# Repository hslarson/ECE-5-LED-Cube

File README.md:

<hr />

## Functionality:
- The cube lights up based on the frequency spectrum of incoming audio
- Each column represents a different frequency
- The stronger the frequency component is, the more LEDs will be on in that column
- Two 3.5mm jacks allow for audio passthrough
- A knob allows for volume control at the output
- The cube will display the volume state whenever the knob is adjusted

<hr />

## Software Details
### Main Program:

- <b> loop </b>
  - Calls the nextLayer() member  function of the Multiplexer class on a preset interval
  - While we wait for the next layer to be drawn, the loop calls the subtasks() function to perform several smaller tasks required to draw the matrix
- <b>subtasks</b>
  - Each subtask referenced in this function is called once for every complete matrix that is sent to the cube. The function must be reset after every iteration
  - The first step (case 0) is calling the checkVolume() member function of the MSGEQ7 class, this decides whether the subtasks function draws a volume matrix or a spectrum matrix
  - Next, we collect the data required to construct the matrix. This is only required if we are drawing a spectrum matrix
  - Then, we construct the matrix itself. This is handled entirely by the respective classes
  - Lastly, we queue the matrix we just drew, meaning that it will be shown in the next iteration of the loop

### Multiplexer Class:

- <b>setMatrix</b>
  - Uses memcpy to either queue a new matrix or allow the queued matrix to be shown
- <b>nextLayer</b>
  - Handles the drawing of individual layers and the queuing of matrices
  - First, calls the constructData() function to format the data in a way that the registers will understand
  - Then, calls the sendData() function to send the data to the cube
- <b>constructData</b>
  - A helper function for nextLayer() that handles the mapping of output pins and the conversion of the resultant binary array to an integer array
- <b>sendToCube</b>
  - Uses the SPI bus to send the data from the constructData() function to the shift registers

### MSGEQ7 Class:

- <b>getSpectrum</b>
  - Reads data from the MSGEQ7 breakout board using analogRead()
- <b>normSpectrum</b>
  - Takes the array from the getSpectrum() function and converts from 7 channels to 36
- <b>makeSpectrumMatrix</b>
  - Maps each frequency band to a specific column of the cube
  - Applies a threshold to the raw reading to decide how many LED’s to light in each column and constructs a Boolean matrix based on this data
- <b>queueMatrix</b>
  - Calls the setMatrix() member of the Multiplexer class to queue the matrix that was built by the makeSpectrumMatrix() function

### VolumeControl Class:

- <b>checkVolume</b>
  - Uses a timer and the getVolume() function to decide whether or not to draw a volume matrix
- <b>getVolume</b>
  - Reads data from the volume potentiometer and normalizes the reading
  - Creates a running average of the normalized readings
- <b>makeVolumeMatrix</b>
  - Takes the current volume reading and creates a Boolean matrix that displays the volume as front-to-back bars that ascend each column then move from left to right to the next column
- <b>queueMatrix</b>
  - Takes the matrix that was constructed by the makeVolumeMatrix and queues it to be shown on the cube

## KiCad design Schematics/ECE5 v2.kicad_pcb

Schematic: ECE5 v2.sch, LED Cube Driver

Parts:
A1: Arduino_Nano_v3.x; Arduino_Nano
C1, C3, C4: 0.1u; C_Disc_D5.0mm_W2.5mm_P2.50mm
C2: 33p; C_Disc_D3.4mm_W2.1mm_P2.50mm
J1, J2: AudioJack3_SwitchTR; 3.5mm_stereo_audio_jack
J3, J4, J6: Conn_02x08_Odd_Even; connector_2x8_male_right_angle
J5: Barrel_Jack_MountingPin; BarrelJack_Horizontal
J7: Conn_01x02_Female; JST_PH_B2B-PH-K_1x02_P2.00mm_Vertical
Q1, Q2, Q3, Q4, Q5, Q6: 2N3904; TO-92_Inline
R1, R2, R3, R4, R5, R6, R7, R8, R9, R10, R11, R12, R15, R16, R17, R18, R21, R22, R23, R24, R25, R26, R27, R28, R29, R30, R31, R32, R33, R34, R35, R36, R37, R38, R39, R40: 470; R_Axial_DIN0207_L6.3mm_D2.5mm_P10.16mm_Horizontal
R13, R14: 22K; R_Axial_DIN0207_L6.3mm_D2.5mm_P10.16mm_Horizontal
R19, R20: 100K; R_Axial_DIN0207_L6.3mm_D2.5mm_P10.16mm_Horizontal
R41, R42, R43, R44, R45, R46: 330; R_Axial_DIN0207_L6.3mm_D2.5mm_P10.16mm_Horizontal
RV1: R_POT_QUAD; potentiometer_quad
SW1: SW_SPDT; toggle_switch_vertical
T1, T2: Transformer_1P_1S; transformer_amazon
U1, U2, U3, U5, U6: 74HC595; DIP-16_W7.62mm_Socket
U4: MSGEQ7; DIP-8_W7.62mm_Socket

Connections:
+5V: C3.1, J7.1, R19.1, RV1.9, SW1.1, U1.10 (~SRCLR), U1.16 (VCC), U2.10 (~SRCLR), U2.16 (VCC), U3.10 (~SRCLR), U3.16 (VCC), U4.1 (VDD), U5.10 (~SRCLR), U5.16 (VCC), U6.10 (~SRCLR), U6.16 (VCC)
EQ_IN: C1.1, U4.5 (IN)
EQ_OUT: A1.20 (A1), U4.3 (OUT)
EQ_RST: A1.11 (D8), U4.7 (RESET)
EQ_STROBE: A1.12 (D9), U4.4 (STROBE)
GND: A1.4 (GND), A1.29 (GND), C2.2, C3.2, C4.2, J5.2, J7.2, Q1.1 (E), Q2.1 (E), Q3.1 (E), Q4.1 (E), Q5.1 (E), Q6.1 (E), RV1.7, T1.3, T2.3, U1.8 (GND), U1.13 (~OE), U2.8 (GND), U2.13 (~OE), U3.8 (GND), U3.13 (~OE), U4.2 (VSS), U5.8 (GND), U5.13 (~OE), U6.8 (GND), U6.13 (~OE)
LYR_1: A1.5 (D2), R41.2
LYR_2: A1.6 (D3), R42.2
LYR_3: A1.7 (D4), R43.2
LYR_4: A1.8 (D5), R44.2
LYR_5: A1.9 (D6), R45.2
LYR_6: A1.10 (D7), R46.2
unnamed: C1.2, R13.1, R14.1
unnamed: C2.1, R20.1, U4.8 (CKIN)
unnamed: C4.1, U4.6 (GND)
unnamed: J1.R, RV1.3, T1.1
unnamed: J1.S, J2.S, RV1.1, RV1.4, T1.2, T2.2
unnamed: J1.T, RV1.6, T2.1
unnamed: J2.R, RV1.2
unnamed: J2.T, RV1.5
unnamed: J3.1, R2.1
unnamed: J3.2, R1.2
unnamed: J3.3, R4.1
unnamed: J3.4, R3.2
unnamed: J3.5, R6.1
unnamed: J3.6, R5.2
unnamed: J3.7, R8.1
unnamed: J3.8, R7.2
unnamed: J3.9, R10.1
unnamed: J3.10, R9.2
unnamed: J3.11, R12.1
unnamed: J3.12, R11.2
unnamed: J3.13, R16.1
unnamed: J3.14, R15.2
unnamed: J3.15, R18.1
unnamed: J3.16, R17.2
unnamed: J4.1, R22.1
unnamed: J4.2, R21.2
unnamed: J4.3, R24.1
unnamed: J4.4, R23.2
unnamed: J4.5, R26.1
unnamed: J4.6, R25.2
unnamed: J4.7, R28.1
unnamed: J4.8, R27.2
unnamed: J4.9, R30.1
unnamed: J4.10, R29.2
unnamed: J4.11, R32.1
unnamed: J4.12, R31.2
unnamed: J4.14, R33.2
unnamed: J4.15, R34.1
unnamed: J5.1, SW1.2
unnamed: J6.1, R36.1
unnamed: J6.2, R35.2
unnamed: J6.3, R38.1
unnamed: J6.4, R37.2
unnamed: J6.5, Q3.3 (C)
unnamed: J6.6, R39.2
unnamed: J6.7, Q6.3 (C)
unnamed: J6.8, Q1.3 (C)
unnamed: J6.9, Q2.3 (C)
unnamed: J6.10, Q4.3 (C)
unnamed: J6.12, Q5.3 (C)
unnamed: J6.15, R40.1
unnamed: Q1.2 (B), R41.1
unnamed: Q2.2 (B), R42.1
unnamed: Q3.2 (B), R43.1
unnamed: Q4.2 (B), R44.1
unnamed: Q5.2 (B), R45.1
unnamed: Q6.2 (B), R46.1
unnamed: R1.1, U1.15 (QA)
unnamed: R2.2, U2.15 (QA)
unnamed: R3.1, U1.1 (QB)
unnamed: R4.2, U2.1 (QB)
unnamed: R5.1, U1.2 (QC)
unnamed: R6.2, U2.2 (QC)
unnamed: R7.1, U1.3 (QD)
unnamed: R8.2, U2.3 (QD)
unnamed: R9.1, U1.4 (QE)
unnamed: R10.2, U2.4 (QE)
unnamed: R11.1, U1.5 (QF)
unnamed: R12.2, U2.5 (QF)
unnamed: R13.2, T1.4
unnamed: R14.2, T2.4
unnamed: R15.1, U1.6 (QG)
unnamed: R16.2, U2.6 (QG)
unnamed: R17.1, U1.7 (QH)
unnamed: R18.2, U2.7 (QH)
unnamed: R19.2, R20.2
unnamed: R21.1, U3.15 (QA)
unnamed: R22.2, U3.7 (QH)
unnamed: R23.1, U3.1 (QB)
unnamed: R24.2, U5.15 (QA)
unnamed: R25.1, U3.2 (QC)
unnamed: R26.2, U5.1 (QB)
unnamed: R27.1, U3.3 (QD)
unnamed: R28.2, U5.2 (QC)
unnamed: R29.1, U3.4 (QE)
unnamed: R30.2, U5.3 (QD)
unnamed: R31.1, U3.5 (QF)
unnamed: R32.2, U5.4 (QE)
unnamed: R33.1, U3.6 (QG)
unnamed: R34.2, U5.5 (QF)
unnamed: R35.1, U5.6 (QG)
unnamed: R36.2, U6.1 (QB)
unnamed: R37.1, U5.7 (QH)
unnamed: R38.2, U6.2 (QC)
unnamed: R39.1, U6.15 (QA)
unnamed: R40.2, U6.3 (QD)
unnamed: U1.9 (QH'), U2.14 (SER)
unnamed: U2.9 (QH'), U3.14 (SER)
unnamed: U3.9 (QH'), U5.14 (SER)
unnamed: U5.9 (QH'), U6.14 (SER)
S_CLK: A1.15 (D12), U1.11 (SRCLK), U2.11 (SRCLK), U3.11 (SRCLK), U5.11 (SRCLK), U6.11 (SRCLK)
S_DATA: A1.14 (D11), U1.14 (SER)
S_LATCH: A1.13 (D10), U1.12 (RCLK), U2.12 (RCLK), U3.12 (RCLK), U5.12 (RCLK), U6.12 (RCLK)
VOL_SENSE: A1.19 (A0), RV1.8

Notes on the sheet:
OUT

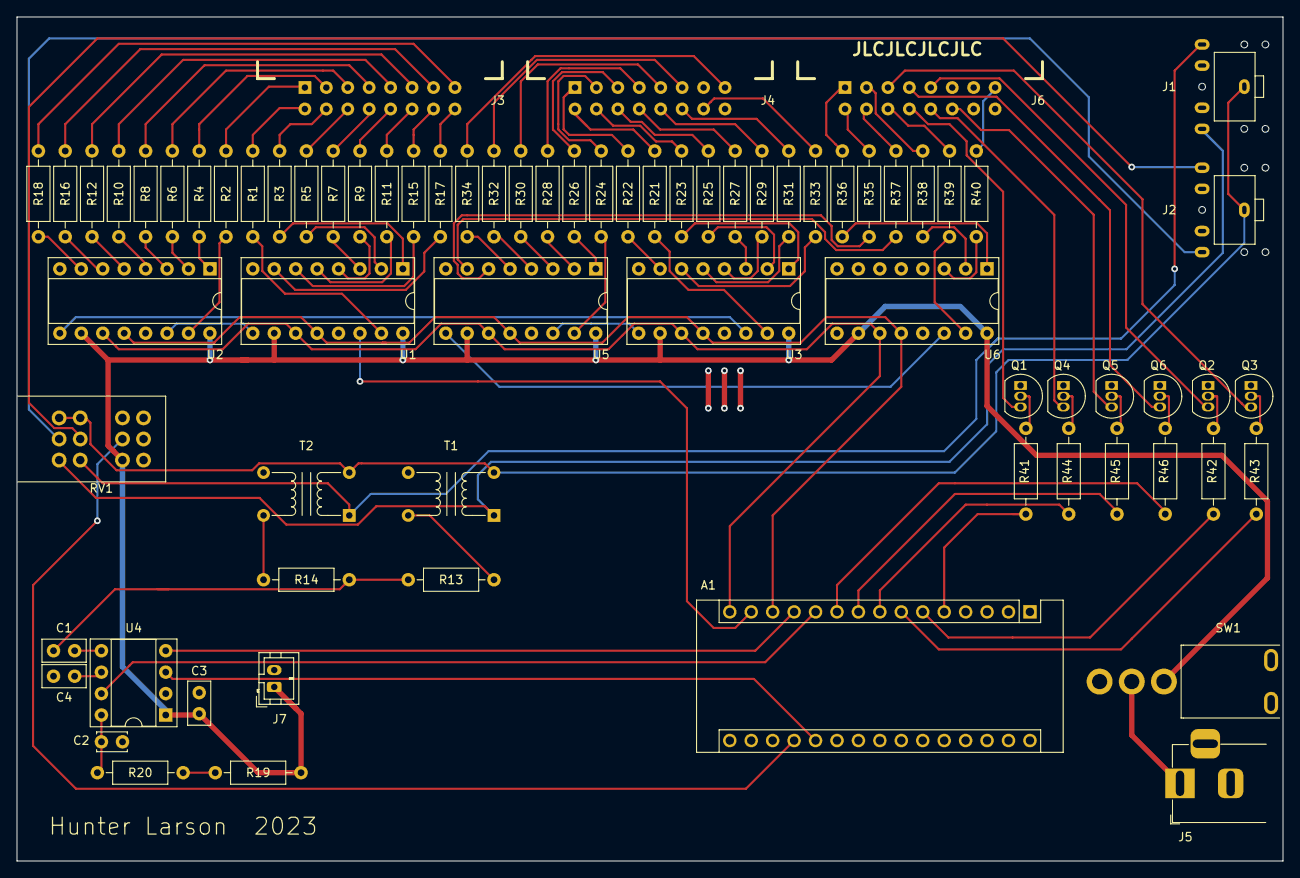
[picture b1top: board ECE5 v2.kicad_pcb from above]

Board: 2 copper layers, 150.0 x 100.0 mm, 74 parts (0 on the bottom side), 116 nets.

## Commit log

2021-02-22 Added function definitions, fixed constants
2021-02-26 Split functions.h into 3 classes
2021-02-26 Cleaned Up
2021-03-02 Minor Improvements
2021-03-05 Completed but Buggy
2021-03-06 Fixed queue bug
2021-03-06 Runs but Untested
2021-03-10 Debugging
2021-03-10 Improvements
2021-03-19 Fixed pin assignments
2021-03-21 Spelling/Formatting
2021-09-12 README Spelling
2021-10-30 Added Pictures
2021-10-31 Pulled project files off gdrive. Not sure if they're current
2022-09-14 Add .gitignore
2022-09-14 Added Updated KiCad Files
2023-04-01 Finalized PCB
2023-07-16 Updated pin definitions and fixed msgeq7 timings
2023-07-16 Renamed folders
2023-09-08 Update pin numbers/constants
2023-09-08 Volume indicator can now show level 0
2025-03-23 Added CAD files
